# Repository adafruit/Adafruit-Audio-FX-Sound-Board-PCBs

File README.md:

# Adafruit Audio FX Sound Boards PCBs
<a href="http://www.adafruit.com/products/2133"><br/>
Click here to purchase one from the Adafruit shop</a>

Would you like to add audio/sound effects to your next project, without an Arduino+Shield? Or maybe you don't even know how to use microcontrollers, you just want to make a sound play whenever you press a button. What about something that has to be small and portable? You are probably feeling a little frustrated: it's been very hard to find a simple, low cost audio effects trigger that is easy to use and does not require any programming

For more details, check out the product pages at

   * https://www.adafruit.com/products/2133
   * https://www.adafruit.com/products/2220
   * https://www.adafruit.com/products/2341
   * https://www.adafruit.com/products/2342
   * https://www.adafruit.com/products/2210
   * https://www.adafruit.com/products/2217
   
PCB files for the Adafruit Audio FX Sound Boards. The format is EagleCAD schematic and board layout

### License

Adafruit invests time and resources providing this open source design, please support Adafruit and open-source hardware by purchasing products from [Adafruit](https://www.adafruit.com)!

All text above must be included in any redistribution

Designed by Limor Fried/Ladyada for Adafruit Industries.
Creative Commons Attribution/Share-Alike, all text above must be included in any redistribution. 
See license.txt for additional information.

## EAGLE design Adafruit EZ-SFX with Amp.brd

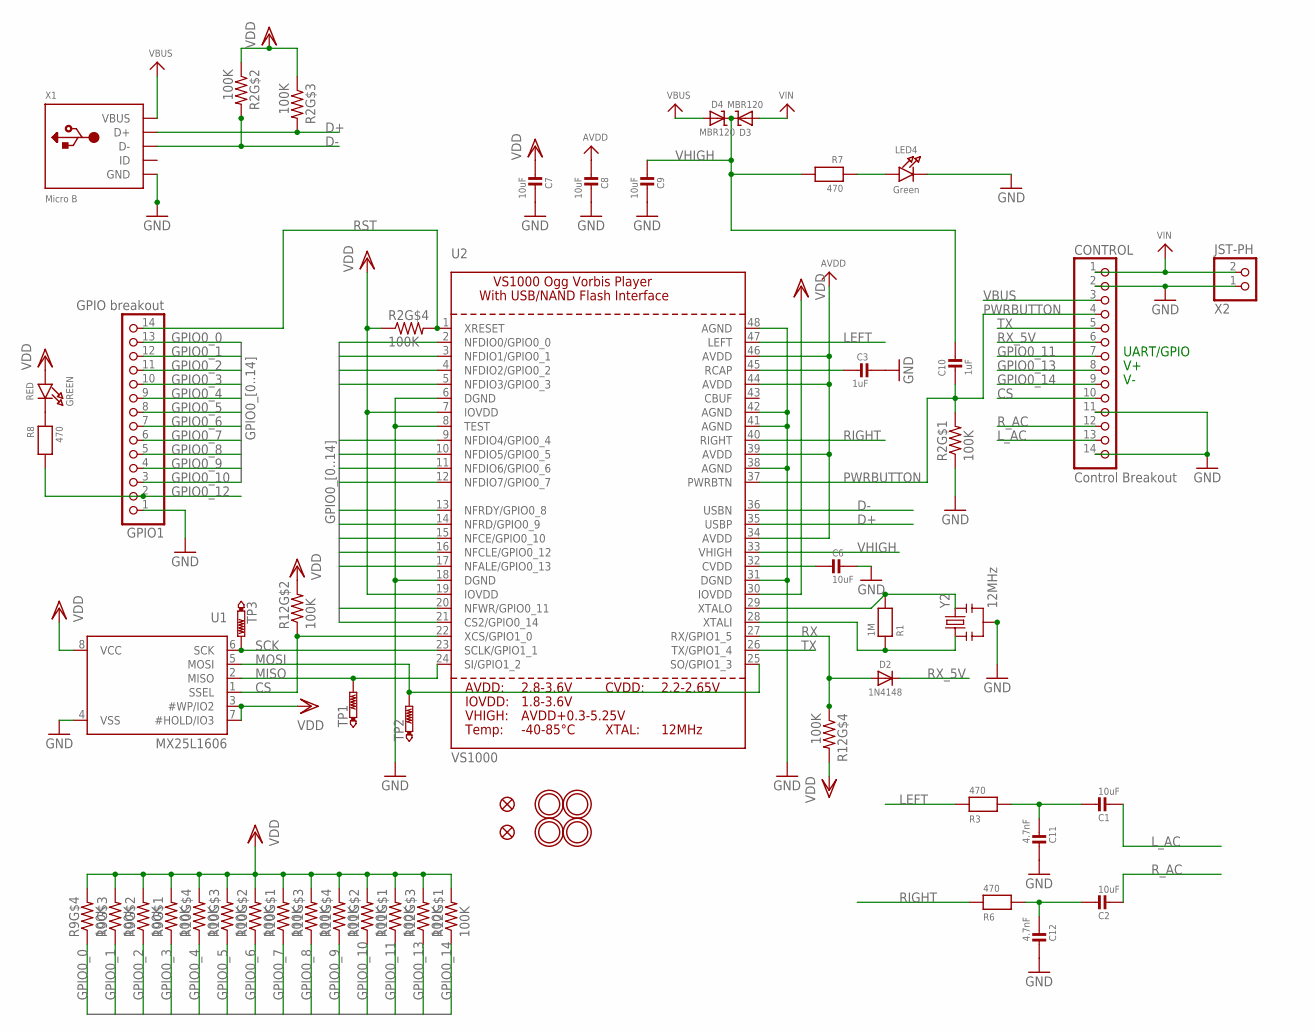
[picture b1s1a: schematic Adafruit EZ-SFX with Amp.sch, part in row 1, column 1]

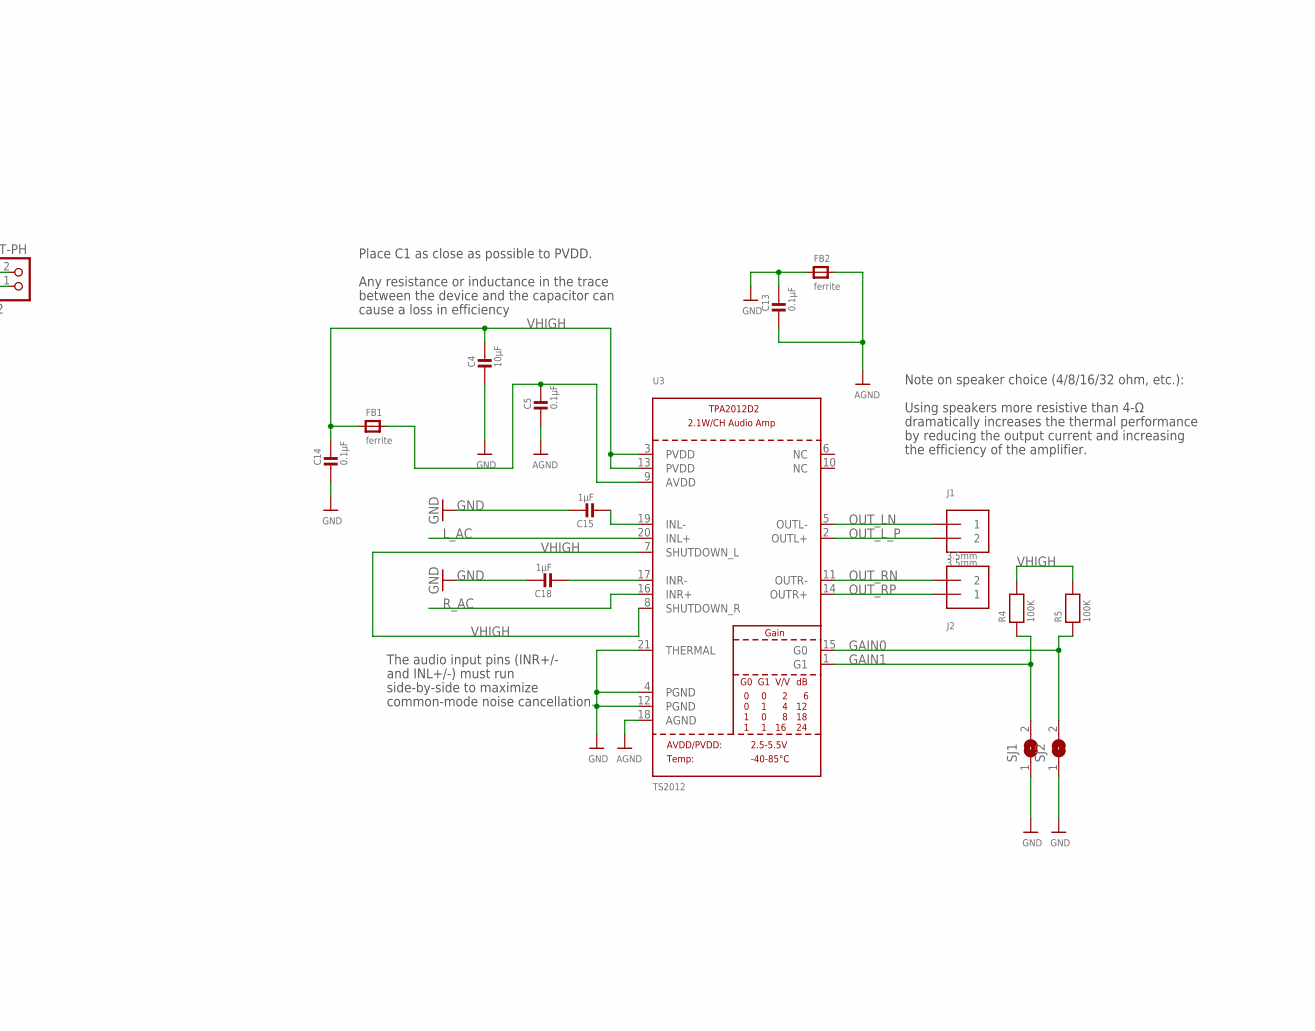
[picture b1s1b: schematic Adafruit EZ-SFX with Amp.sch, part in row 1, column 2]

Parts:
C1, C8, C9: 10uF; 0805-NO
C2, C6, C7: 10uF; 0805_10MGAP
C3, C10: 1uF; 0805-NO
C4: 10µF; 0805-NO
C5, C13, C14: 0.1µF; 0805-NO
C11, C12: 4.7nF; 0805-NO
C15, C18: 1µF; 0805-NO
CONTROL: Control Breakout; 1X14-CB
D2: 1N4148; SOD-323
D3, D4: MBR120; SOD-123
FB1, FB2: ferrite; _0805MP
FID1, FID2: FIDUCIAL""; FIDUCIAL_1MM
GPIO1: GPIO breakout; 1X14-CB
GREEN: RED; CHIPLED_0805_NOOUTLINE
J1, J2: 3.5mm; TERMBLOCK_1X2-3.5MM
LED4: Green; CHIPLED_0805_NOOUTLINE
R1: 1M; 0805-NO
R2, R9, R10, R11, R12: 100K; RESPACK_4X0603
R3, R6, R7, R8: 470; 0805-NO
R4, R5: 100K; 0805-NO
SJ1: SOLDERJUMPER; SOLDERJUMPER_ARROW_NOPASTE
SJ2: SOLDERJUMPERCLOSED; SOLDERJUMPER_CLOSEDWIRE
TP1, TP2, TP3: PTR1B1,27; B1,27
U1: MX25L1606; SOIC8_208MIL
U2: VS1000; LQFP48
U3: TS2012; WQFN20
U$5, U$6, U$7, U$8: MOUNTINGHOLE2.5; MOUNTINGHOLE_2.5_PLATED
X1: Micro B; 4UCONN_20329
X2: JST-PH; JSTPH2
Y2: 12MHz; RESONATOR-SMD

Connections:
AGND: C5.2, C13.2, FB2.2, U3.18 (AGND)
AVDD: C8.2, U2.34 (AVDD), U2.39 (AVDD), U2.44 (AVDD), U2.46 (AVDD)
CS: CONTROL.10, R12.2 (1), U1.1 (SSEL), U2.22 (XCS/GPIO1_0)
D+: R2.6 (2), U2.35 (USBP), X1.D+
D-: R2.7 (2), U2.36 (USBN), X1.D-
GAIN0: R5.1, SJ2.2, U3.15 (G0)
GAIN1: R4.1, SJ1.2, U3.1 (G1)
GND: C3.2, C4.2, C6.1, C7.1, C8.1, C9.1, C11.2, C12.2, C13.1, C14.2, C15.1, C18.1, CONTROL.2, CONTROL.11, CONTROL.14, FB2.1, GPIO1.1, LED4.C, R2.1, SJ1.1, SJ2.1, U1.4 (VSS), U2.6 (DGND), U2.8 (TEST), U2.18 (DGND), U2.31 (DGND), U2.38 (AGND), U2.41 (AGND), U2.42 (AGND), U2.48 (AGND), U3.4 (PGND), U3.12 (PGND), U3.21 (THERMAL), X1.BASE@1 (GND), X1.BASE@2 (GND), X1.GND, X1.SPRT@1 (GND), X1.SPRT@2 (GND), X1.SPRT@3 (GND), X1.SPRT@4 (GND), X2.1, Y2.2
GPIO0_0: GPIO1.13, R9.4 (1), U2.2 (NFDIO0/GPIO0_0)
GPIO0_1: GPIO1.12, R9.3 (1), U2.3 (NFDIO1/GPIO0_1)
GPIO0_2: GPIO1.11, R9.2 (1), U2.4 (NFDIO2/GPIO0_2)
GPIO0_3: GPIO1.10, R9.1, U2.5 (NFDIO3/GPIO0_3)
GPIO0_4: GPIO1.9, R10.4 (1), U2.9 (NFDIO4/GPIO0_4)
GPIO0_5: GPIO1.8, R10.3 (1), U2.10 (NFDIO5/GPIO0_5)
GPIO0_6: GPIO1.7, R10.2 (1), U2.11 (NFDIO6/GPIO0_6)
GPIO0_7: GPIO1.6, R10.1, U2.12 (NFDIO7/GPIO0_7)
GPIO0_8: GPIO1.5, R11.3 (1), U2.13 (NFRDY/GPIO0_8)
GPIO0_9: GPIO1.4, R11.4 (1), U2.14 (NFRD/GPIO0_9)
GPIO0_10: GPIO1.3, R11.2 (1), U2.15 (NFCE/GPIO0_10)
GPIO0_11: CONTROL.7, R11.1, U2.20 (NFWR/GPIO0_11)
GPIO0_12: GPIO1.2, R8.2, U2.16 (NFCLE/GPIO0_12)
GPIO0_13: CONTROL.8, R12.3 (1), U2.17 (NFALE/GPIO0_13)
GPIO0_14: CONTROL.9, R12.1, U2.21 (CS2/GPIO0_14)
LEFT: R3.1, U2.47 (LEFT)
L_AC: C1.1, CONTROL.13, U3.20 (INL+)
MISO: TP1.TP, U1.2 (MISO), U2.24 (SI/GPIO1_2)
MOSI: TP2.TP, U1.5 (MOSI), U2.25 (SO/GPIO1_3)
unnamed: LED4.A, R7.1
unnamed: C2.2, C12.1, R6.2
unnamed: C3.1, U2.45 (RCAP)
unnamed: R1.2, U2.29 (XTALO), Y2.3
unnamed: C6.2, U2.32 (CVDD)
unnamed: C1.2, C11.1, R3.2
unnamed: C5.1, FB1.2, U3.9 (AVDD)
unnamed: GREEN.C, R8.1
unnamed: C15.2, U3.19 (INL-)
unnamed: C18.2, U3.17 (INR-)
unnamed: R1.1, U2.28 (XTALI), Y2.1
OUT_LN: J1.1, U3.5 (OUTL-)
OUT_L_P: J1.2, U3.2 (OUTL+)
OUT_RN: J2.2, U3.11 (OUTR-)
OUT_RP: J2.1, U3.14 (OUTR+)
PWRBUTTON: C10.1, CONTROL.4, R2.8 (2), U2.37 (PWRBTN)
RIGHT: R6.1, U2.40 (RIGHT)
RST: GPIO1.14, R2.5 (2), U2.1 (XRESET)
RX: D2.A, R12.4 (1), U2.27 (RX/GPIO1_5)
RX_5V: CONTROL.6, D2.C
R_AC: C2.1, CONTROL.12, U3.16 (INR+)
SCK: TP3.TP, U1.6 (SCK), U2.23 (SCLK/GPIO1_1)
TX: CONTROL.5, U2.26 (TX/GPIO1_4)
VBUS: CONTROL.3, D4.A, X1.VBUS
VDD: C7.2, GREEN.A, R2.2 (1), R2.3 (1), R2.4 (1), R9.5 (2), R9.6 (2), R9.7 (2), R9.8 (2), R10.5 (2), R10.6 (2), R10.7 (2), R10.8 (2), R11.5 (2), R11.6 (2), R11.7 (2), R11.8 (2), R12.5 (2), R12.6 (2), R12.7 (2), R12.8 (2), U1.3 (#WP/IO2), U1.7 (#HOLD/IO3), U1.8 (VCC), U2.7 (IOVDD), U2.19 (IOVDD), U2.30 (IOVDD)
VHIGH: C4.1, C9.2, C10.2, C14.1, D3.C, D4.C, FB1.1, R4.2, R5.2, R7.2, U2.33 (VHIGH), U3.3 (PVDD), U3.7 (SHUTDOWN_L), U3.8 (SHUTDOWN_R), U3.13 (PVDD)
VIN: CONTROL.1, D3.A, X2.2

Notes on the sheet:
UART/GPIO
Place C1 as close as possible to PVDD.
Any resistance or inductance in the trace
between the device and the capacitor can
cause a loss in efficiency
Using speakers more resistive than 4-Ω
dramatically increases the thermal performance
by reducing the output current and increasing
the efficiency of the amplifier.
Note on speaker choice (4/8/16/32 ohm, etc.):
The audio input pins (INR+/-
and INL+/-) must run
side-by-side to maximize
common-mode noise cancellation.

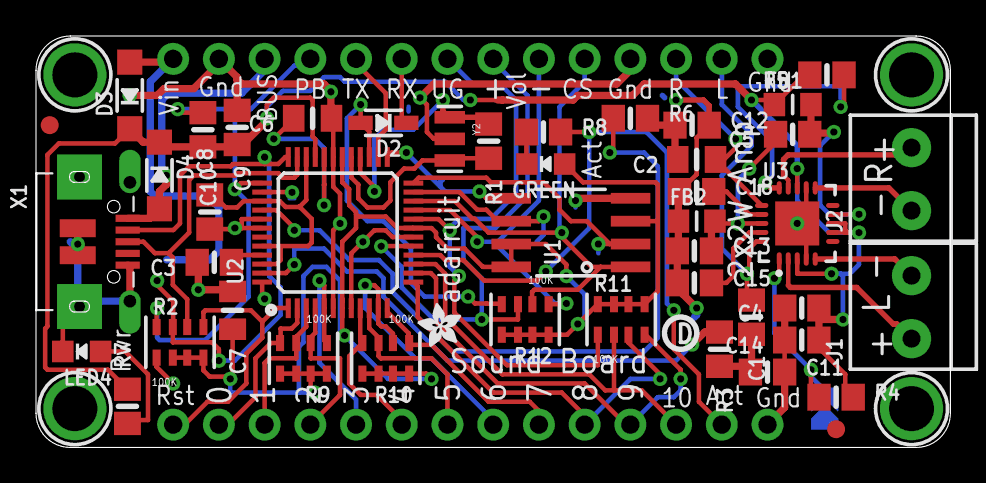
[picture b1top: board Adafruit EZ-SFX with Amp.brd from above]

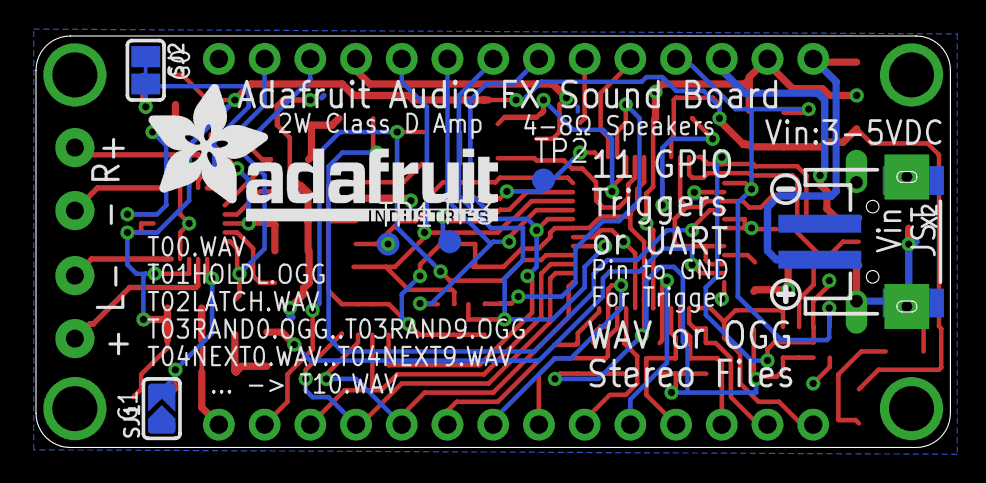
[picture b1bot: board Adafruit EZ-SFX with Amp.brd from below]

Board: 2 copper layers, 50.8 x 22.9 mm, 61 parts (9 on the bottom side), 54 nets.

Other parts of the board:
U$11: ADAFRUIT_2.5MM
U$12: SYMBOL_PLUS
U$13: SYMBOL_MINUS
U$14: ADAFRUIT_TEXT_20MM
U$15: PCBFEAT-REV-040

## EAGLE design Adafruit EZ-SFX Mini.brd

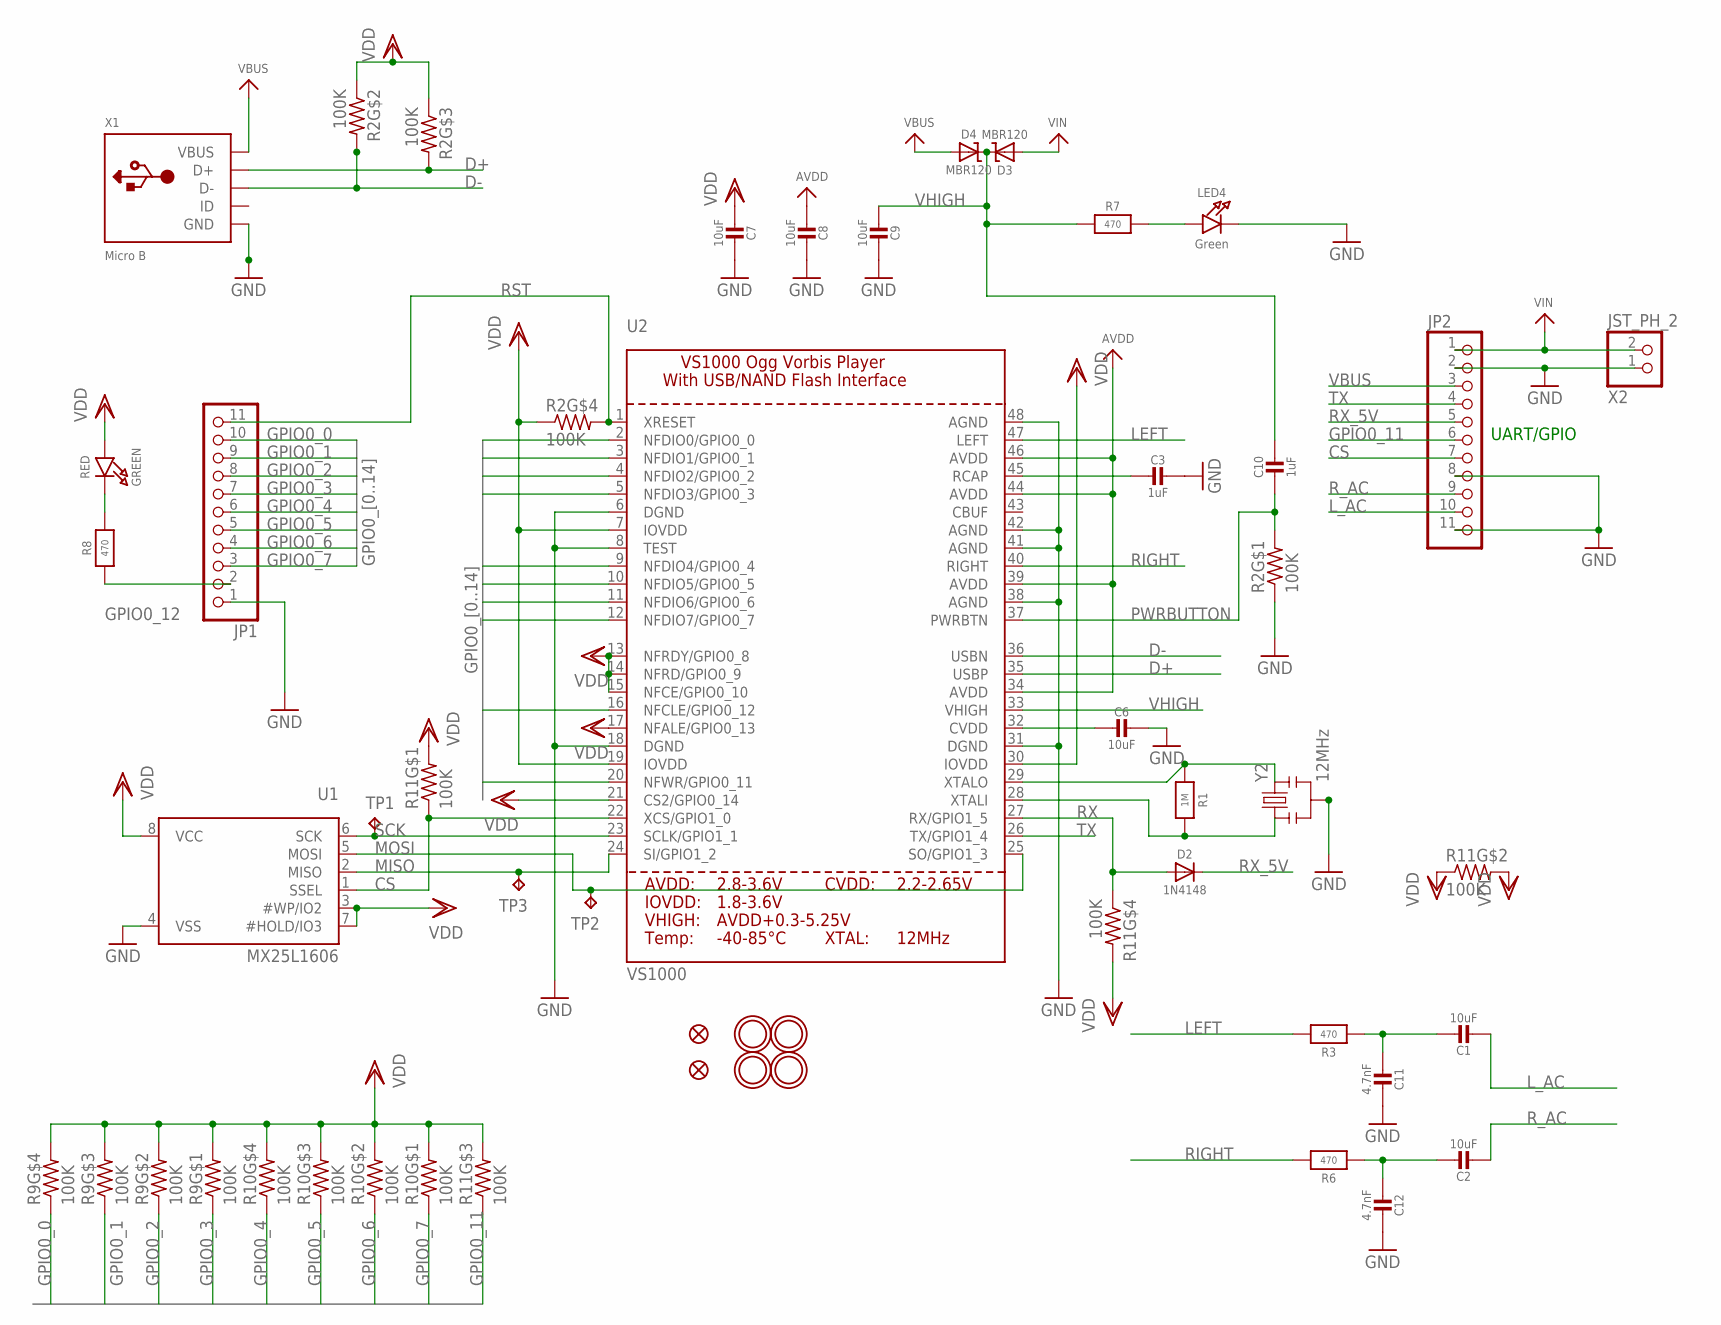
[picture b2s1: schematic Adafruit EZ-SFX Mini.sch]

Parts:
C1, C2, C8, C9: 10uF; 0805-NO
C3, C10: 1uF; 0805-NO
C6, C7: 10uF; 0805_10MGAP
C11, C12: 4.7nF; 0805-NO
D2: 1N4148; SOD-323
D3, D4: MBR120; SOD-123
FID1, FID2: FIDUCIAL""; FIDUCIAL_1MM
GREEN: RED; CHIPLED_0805_NOOUTLINE
JP1, JP2: HEADER-1X1176MIL; 1X11_ROUND_76
LED4: Green; CHIPLED_0805_NOOUTLINE
R1: 1M; _0805MP
R2, R9, R10, R11: 100K; RESPACK_4X0603
R3, R6, R7, R8: 470; 0805-NO
TP1, TP2, TP3: TPB1,27; B1,27
U1: MX25L1606; SOIC8_208MIL
U2: VS1000; LQFP48
U$5, U$6, U$7, U$8: MOUNTINGHOLE2.5; MOUNTINGHOLE_2.5_PLATED
X1: Micro B; 4UCONN_20329_V2
X2: JST_PH_2; JSTPH2
Y2: 12MHz; RESONATOR-SMD

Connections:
AVDD: C8.2, U2.34 (AVDD), U2.39 (AVDD), U2.44 (AVDD), U2.46 (AVDD)
CS: JP2.7, R11.1, U1.1 (SSEL), U2.22 (XCS/GPIO1_0)
D+: R2.6 (2), U2.35 (USBP), X1.D+
D-: R2.7 (2), U2.36 (USBN), X1.D-
GND: C3.2, C6.1, C7.1, C8.1, C9.1, C11.2, C12.2, JP1.1, JP2.2, JP2.8, JP2.11, LED4.C, R2.1, U1.4 (VSS), U2.6 (DGND), U2.8 (TEST), U2.18 (DGND), U2.31 (DGND), U2.38 (AGND), U2.41 (AGND), U2.42 (AGND), U2.48 (AGND), X1.BASE@1 (GND), X1.BASE@2 (GND), X1.GND, X1.SPRT@1 (GND), X1.SPRT@2 (GND), X1.SPRT@3 (GND), X1.SPRT@4 (GND), X2.1, Y2.2
GPIO0_0: JP1.10, R9.4 (1), U2.2 (NFDIO0/GPIO0_0)
GPIO0_1: JP1.9, R9.3 (1), U2.3 (NFDIO1/GPIO0_1)
GPIO0_2: JP1.8, R9.2 (1), U2.4 (NFDIO2/GPIO0_2)
GPIO0_3: JP1.7, R9.1, U2.5 (NFDIO3/GPIO0_3)
GPIO0_4: JP1.6, R10.4 (1), U2.9 (NFDIO4/GPIO0_4)
GPIO0_5: JP1.5, R10.3 (1), U2.10 (NFDIO5/GPIO0_5)
GPIO0_6: JP1.4, R10.2 (1), U2.11 (NFDIO6/GPIO0_6)
GPIO0_7: JP1.3, R10.1, U2.12 (NFDIO7/GPIO0_7)
GPIO0_11: JP2.6, R11.3 (1), U2.20 (NFWR/GPIO0_11)
GPIO0_12: JP1.2, R8.2, U2.16 (NFCLE/GPIO0_12)
LEFT: R3.1, U2.47 (LEFT)
L_AC: C1.1, JP2.10
MISO: TP3.TP, U1.2 (MISO), U2.24 (SI/GPIO1_2)
MOSI: TP2.TP, U1.5 (MOSI), U2.25 (SO/GPIO1_3)
unnamed: LED4.A, R7.1
unnamed: C2.2, C12.1, R6.2
unnamed: C3.1, U2.45 (RCAP)
unnamed: R1.2, U2.29 (XTALO), Y2.3
unnamed: C6.2, U2.32 (CVDD)
unnamed: C1.2, C11.1, R3.2
unnamed: GREEN.C, R8.1
unnamed: R1.1, U2.28 (XTALI), Y2.1
PWRBUTTON: C10.1, R2.8 (2), U2.37 (PWRBTN)
RIGHT: R6.1, U2.40 (RIGHT)
RST: JP1.11, R2.5 (2), U2.1 (XRESET)
RX: D2.A, R11.4 (1), U2.27 (RX/GPIO1_5)
RX_5V: D2.C, JP2.5
R_AC: C2.1, JP2.9
SCK: TP1.TP, U1.6 (SCK), U2.23 (SCLK/GPIO1_1)
TX: JP2.4, U2.26 (TX/GPIO1_4)
VBUS: D4.A, JP2.3, X1.VBUS
VDD: C7.2, GREEN.A, R2.2 (1), R2.3 (1), R2.4 (1), R9.5 (2), R9.6 (2), R9.7 (2), R9.8 (2), R10.5 (2), R10.6 (2), R10.7 (2), R10.8 (2), R11.2 (1), R11.5 (2), R11.6 (2), R11.7 (2), R11.8 (2), U1.3 (#WP/IO2), U1.7 (#HOLD/IO3), U1.8 (VCC), U2.7 (IOVDD), U2.13 (NFRDY/GPIO0_8), U2.14 (NFRD/GPIO0_9), U2.15 (NFCE/GPIO0_10), U2.17 (NFALE/GPIO0_13), U2.19 (IOVDD), U2.21 (CS2/GPIO0_14), U2.30 (IOVDD)
VHIGH: C9.2, C10.2, D3.C, D4.C, R7.2, U2.33 (VHIGH)
VIN: D3.A, JP2.1, X2.2

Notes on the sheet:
UART/GPIO

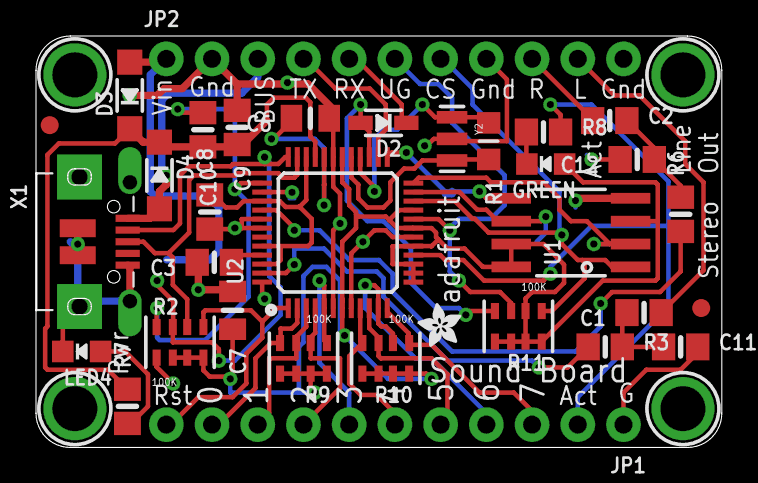
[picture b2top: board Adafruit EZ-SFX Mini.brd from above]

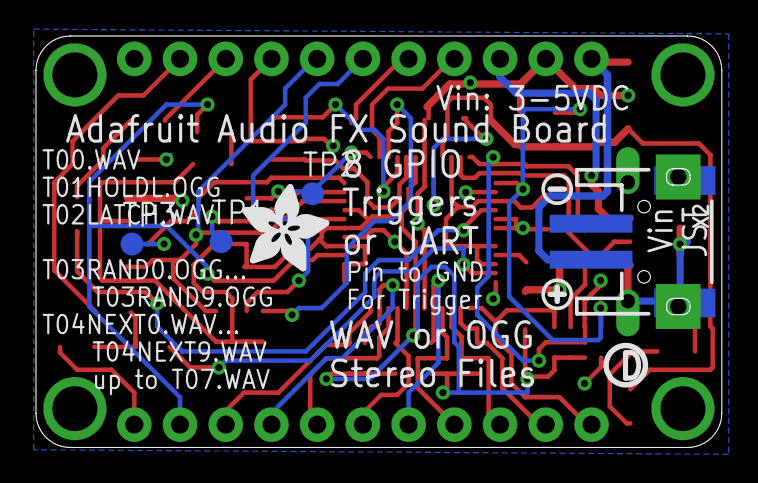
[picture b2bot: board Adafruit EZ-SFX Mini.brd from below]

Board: 2 copper layers, 38.1 x 22.9 mm, 45 parts (8 on the bottom side), 39 nets.

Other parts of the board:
U$11: ADAFRUIT_2.5MM
U$12: SYMBOL_PLUS
U$13: SYMBOL_MINUS
U$14: ADAFRUIT_5MM
U$15: PCBFEAT-REV-056

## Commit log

2016-06-21 Add all 3 versions

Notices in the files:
parts and their libraries:
microbuilder: This work is placed in the public domain, and may be freely used for commercial and non-commercial work with the following conditions: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
SparkFun: Licensing: CC v3.0 Share-Alike You are welcome to use this library for commercial purposes.
